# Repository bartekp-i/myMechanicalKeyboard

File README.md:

# 75% Custom Mechanical Keyboard PCB Documentation  
**A compact, RP2040-powered keyboard with USB-C and OLED support.**  

---

## Overview  
This project is a custom 75% mechanical keyboard PCB designed around the Raspberry Pi RP2040 microcontroller. It features a non-standard QWERTY layout with 83 keys, USB-C connectivity with robust signal filtering, ESD protection, and support for a 0.96-inch RGB OLED module. The PCB is manufactured by JLCPCB and ready for soldering and programming.  

---

## Features  
- **RP2040 Microcontroller**: Dual-core ARM Cortex-M0+ for flexible firmware customization.  
- **USB-C Connectivity**: Built-in signal filtering and ESD protection (TVS diode) on D+/D- lines.  
- **Power Regulation**: 3.3V LDO Regulator (SPX5205M5-L-3-3/TR) for stable power delivery.  
- **QSPI Flash**: W25Q16JVUXIQ (2MB) for firmware storage.  
- **Precision Timing**: ABM8-272-T3 12MHz crystal oscillator.  
- **OLED Support**: Pads/THT headers for a 0.96-inch RGB OLED module.  
- **Debugging**: SWD (Serial Wire Debug) pins for firmware flashing/troubleshooting.  
- **Mechanical Design**:  
  - 75% layout (83 keys).  
  - Custom plate and back panel.  
  - Stabilizers for Space, Shift, Enter, and Backspace keys.  
  - AKKO V3 Pro Yellow switches (pre-lubed linear).  
  - Switching diodes for every key (anti-ghosting).  

---

## Hardware Details  

### RP2040 Microcontroller  
- Handles key matrix scanning, USB communication, and peripheral control.  
- Connected peripherals:  
  - **QSPI Flash**: Stores firmware and configuration data.  
  - **ABM8-272-T3 Oscillator**: Provides precise timing for USB communication.  
  - **Boot Button**: For entering firmware update mode.  
  - **SWD Pins**: 1x3 header for programming/debugging.  

### USB-C and Signal Integrity  
- **ESD Protection**: TVS diodes on D+/D- lines to protect against electrostatic discharge.  
- **Filtering**: Ferrite beads/RC filters to reduce noise on data lines.  

### Power Regulation  
- **SPX5205M5-L-3-3/TR LDO**: Converts USB 5V to 3.3V for RP2040 and peripherals.  
- Max current: 150mA (sufficient for RP2040, OLED, and peripherals).  

### Keyboard Matrix  
- **83-Key Layout**: Non-standard 75% design (see `Layout/` directory for matrix mapping).  
- **Switching Diodes**: Each key has a diode (1N4148 or similar) to prevent "ghosting" by blocking reverse current in the matrix.  

### Stabilizers  
- Required for longer keys: Spacebar, Enter, Backspace, and Shift (supports Cherry-style stabilizers).  

### OLED Module  
- **0.96-inch RGB OLED**: Connected via SPI.  
- Mounting: THT pads or header pins for secure attachment.
- Finally I decided to not use it due to current draw considerations. 

---

## Design & Manufacturing  
- **PCB**: Designed in KiCad (files in `Hardware/`).   
- **Manufacturing**:  
  - JLCPCB 2-layer PCB with white solder mask finish.  
  - SMD components can be pre-soldered.  

---

## Firmware  
- Coded using *QMK*-RP2040 is compatible with this software.  
- Example firmware available in `Firmware/`.  

---

## Build Instructions  
1. **Solder Components**:  
   - Diodes (orient cathode stripe correctly).  
   - RP2040, USB-C port, oscillator, and regulator.  
   - SWD header and OLED pins.  
2. **Mount Stabilizers**: Clip-in Cherry stabilizers for large keys.  
3. **Install Switches**: Secure AKKO V3 Pro switches into the plate and solder to PCB.  
4. **Attach OLED**: Solder headers or directly mount the OLED module.  
5. **Flash Firmware**: Use SWD or UF2 bootloader (press boot button while plugging in USB).  

---

## Acknowledgements  
- JLCPCB for PCB manufacturing.  
- Raspberry Pi Foundation for RP2040.  

## 📸 Photos!  

**Keyboard layout** 

**Schematic** 

**PCB Layout**

**Keyboard Plate**

**Back Plate**

**3D PCB Layout**

**3D Keyboard Plate**

**3D Back Plate**

**Boards After Manufacturing**

**Fully Assembled Product**

---  
*Designed with Kicad by Bartosz Piotrowski.*

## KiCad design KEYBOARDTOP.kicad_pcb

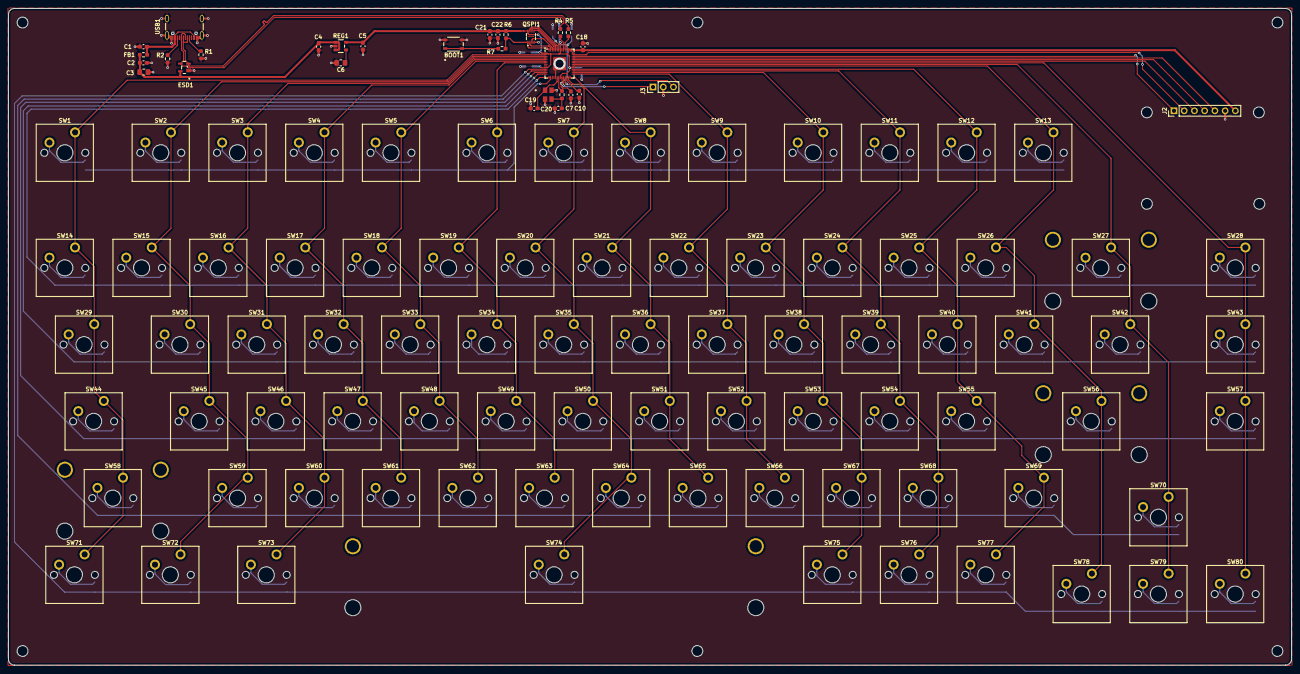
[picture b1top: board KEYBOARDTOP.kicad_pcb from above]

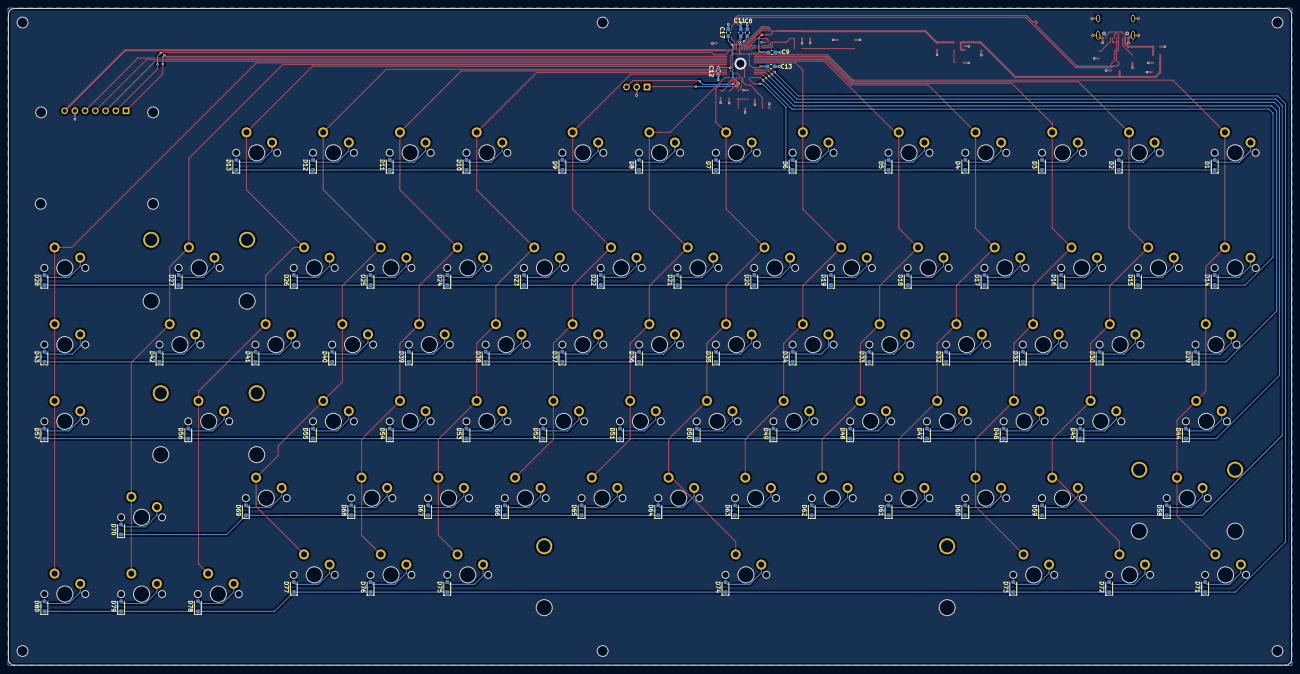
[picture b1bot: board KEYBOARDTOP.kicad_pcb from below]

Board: 2 copper layers, 318.5 x 163.0 mm, 200 parts (86 on the bottom side), 130 nets.

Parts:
BOOT1: SKRPABE010; SW4_SKRPABE010_ALPS
C1: 10nF; C_0603_1608Metric_Pad1.08x0.95mm_HandSolder
C2: 0.1uF; C_0603_1608Metric_Pad1.08x0.95mm_HandSolder
C3: 10uF; C_0805_2012Metric_Pad1.18x1.45mm_HandSolder
C4, C5: 1uF; C_0603_1608Metric_Pad1.08x0.95mm_HandSolder
C6: NO-FIT(10u); C_0805_2012Metric_Pad1.18x1.45mm_HandSolder
C7, C8, C9, C10, C11, C12, C13, C21: 100n; C_0603_1608Metric_Pad1.08x0.95mm_HandSolder
C17, C18: 1u; C_0603_1608Metric_Pad1.08x0.95mm_HandSolder
C19, C20: 15pF; C_0603_1608Metric_Pad1.08x0.95mm_HandSolder
C22: 2u2; C_0603_1608Metric_Pad1.08x0.95mm_HandSolder
D1, D2, D3, D4, D5, D6, D7, D8, D9, D10, D11, D12, D13, D14, D15, D16, D17, D18, D19, D20, D21, D22, D23, D24, D25, D26, D27, D28, D29, D30, D31, D32, D33, D34, D35, D36, D37, D38, D39, D40, D41, D42, D43, D44, D45, D46, D47, D48, D49, D50, D51, D52, D53, D54, D55, D56, D57, D58, D59, D60, D61, D62, D63, D64, D65, D66, D67, D68, D69, D70, D71, D72, D73, D74, D75, D76, D77, D78, D79, D80: D_Small; D_SOD-323_HandSoldering
ESD1: PRTR5V0U2X_215; SOT143B_PRTR5V0U2X_215_NEX
FB1: 120/100MHZ; R_0603_1608Metric_Pad0.98x0.95mm_HandSolder
J2: Conn_01x07; PinHeader_1x07_P2.54mm_Vertical
J3: Conn_01x03; PinHeader_1x03_P2.54mm_Vertical
QSPI1: W25Q16JVUXIQ; W25Q16JVUXIQ_WIN
R1, R2: 5.1k; R_0603_1608Metric_Pad0.98x0.95mm_HandSolder
R3: 1k; R_0603_1608Metric_Pad0.98x0.95mm_HandSolder
R4, R5: 27R; R_0603_1608Metric_Pad0.98x0.95mm_HandSolder
R6: No-Fit(1k); R_0603_1608Metric_Pad0.98x0.95mm_HandSolder
R7: 1K; R_0603_1608Metric_Pad0.98x0.95mm_HandSolder
REG1: SPX5205M5-L-3-3/TR; SP6201EM5
S1: MX_stab; STAB_MX_P_6.25u
S2: MX_stab; STAB_MX_P_2u
S3, S4: MX_stab; STAB_MX_P_2.25u
SW1: ESC; SW_Cherry_MX_PCB_1.00u
SW2: F1; SW_Cherry_MX_PCB_1.00u
SW3: F2; SW_Cherry_MX_PCB_1.00u
SW4: F3; SW_Cherry_MX_PCB_1.00u
SW5: F4; SW_Cherry_MX_PCB_1.00u
SW6: F5; SW_Cherry_MX_PCB_1.00u
SW7: F6; SW_Cherry_MX_PCB_1.00u
SW8: F7; SW_Cherry_MX_PCB_1.00u
SW9: F8; SW_Cherry_MX_PCB_1.00u
SW10: F9; SW_Cherry_MX_PCB_1.00u
SW11: F10; SW_Cherry_MX_PCB_1.00u
SW12: F11; SW_Cherry_MX_PCB_1.00u
SW13: F12; SW_Cherry_MX_PCB_1.00u
SW14: "~`"; SW_Cherry_MX_PCB_1.00u
SW15: 1; SW_Cherry_MX_PCB_1.00u
SW16: 2; SW_Cherry_MX_PCB_1.00u
SW17: 3; SW_Cherry_MX_PCB_1.00u
SW18: 4; SW_Cherry_MX_PCB_1.00u
SW19: 5; SW_Cherry_MX_PCB_1.00u
SW20: 6; SW_Cherry_MX_PCB_1.00u
SW21: 7; SW_Cherry_MX_PCB_1.00u
SW22: 8; SW_Cherry_MX_PCB_1.00u
SW23: 9; SW_Cherry_MX_PCB_1.00u
SW24: 0; SW_Cherry_MX_PCB_1.00u
SW25: -; SW_Cherry_MX_PCB_1.00u
SW26: +; SW_Cherry_MX_PCB_1.00u
SW27: backspace; SW_Cherry_MX_PCB_2.00u
SW28: pg_up; SW_Cherry_MX_PCB_1.00u
SW29: tab; SW_Cherry_MX_PCB_1.50u
SW30: q; SW_Cherry_MX_PCB_1.00u
SW31: w; SW_Cherry_MX_PCB_1.00u
SW32: e; SW_Cherry_MX_PCB_1.00u
SW33: r; SW_Cherry_MX_PCB_1.00u
SW34: t; SW_Cherry_MX_PCB_1.00u
SW35: y; SW_Cherry_MX_PCB_1.00u
SW36: u; SW_Cherry_MX_PCB_1.00u
SW37: i; SW_Cherry_MX_PCB_1.00u
SW38: o; SW_Cherry_MX_PCB_1.00u
SW39: p; SW_Cherry_MX_PCB_1.00u
SW40: [; SW_Cherry_MX_PCB_1.00u
SW41: ]; SW_Cherry_MX_PCB_1.00u
SW42: |; SW_Cherry_MX_PCB_1.50u
SW43: pg_down; SW_Cherry_MX_PCB_1.00u
SW44: caps; SW_Cherry_MX_PCB_1.75u
SW45: a; SW_Cherry_MX_PCB_1.00u
SW46: s; SW_Cherry_MX_PCB_1.00u
SW47: d; SW_Cherry_MX_PCB_1.00u
SW48: f; SW_Cherry_MX_PCB_1.00u
SW49: g; SW_Cherry_MX_PCB_1.00u
SW50: h; SW_Cherry_MX_PCB_1.00u
SW51: j; SW_Cherry_MX_PCB_1.00u
SW52: k; SW_Cherry_MX_PCB_1.00u
SW53: l; SW_Cherry_MX_PCB_1.00u
SW54: :; SW_Cherry_MX_PCB_1.00u
SW55: "; SW_Cherry_MX_PCB_1.00u
SW56: enter; SW_Cherry_MX_PCB_2.25u
SW57: delete; SW_Cherry_MX_PCB_1.00u
SW58: shift; SW_Cherry_MX_PCB_2.25u
SW59: z; SW_Cherry_MX_PCB_1.00u
SW60: x; SW_Cherry_MX_PCB_1.00u
SW61: c; SW_Cherry_MX_PCB_1.00u
SW62: v; SW_Cherry_MX_PCB_1.00u
SW63: b; SW_Cherry_MX_PCB_1.00u
SW64: n; SW_Cherry_MX_PCB_1.00u
SW65: m; SW_Cherry_MX_PCB_1.00u
SW66: <; SW_Cherry_MX_PCB_1.00u
SW67: >; SW_Cherry_MX_PCB_1.00u
SW68: ?; SW_Cherry_MX_PCB_1.00u
SW69: shift_2; SW_Cherry_MX_PCB_1.75u
SW70: arrow_up; SW_Cherry_MX_PCB_1.00u
SW71: ctrl; SW_Cherry_MX_PCB_1.25u
SW72: windows; SW_Cherry_MX_PCB_1.25u
SW73: alt; SW_Cherry_MX_PCB_1.25u
SW74: spacebar; SW_Cherry_MX_PCB_6.25u
SW75: alt; SW_Cherry_MX_PCB_1.00u
SW76: fn; SW_Cherry_MX_PCB_1.00u
SW77: ctrl; SW_Cherry_MX_PCB_1.00u
SW78: arrow_left; SW_Cherry_MX_PCB_1.00u
SW79: arrow_down; SW_Cherry_MX_PCB_1.00u
SW80: arrow_right; SW_Cherry_MX_PCB_1.00u
U3: RP2040; QFN-56-1EP_7x7mm_P0.4mm_EP3.2x3.2mm
USB1: USB_C_Receptacle_USB2.0_16P; USB_C_Receptacle_GCT_USB4105-xx-A_16P_TopMnt_Horizontal
X1: ABM8-272-T3; ABM8-272-T3_ABR

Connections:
+1.1V: C7.1, C8.1, C17.1, U3.23 (DVDD), U3.45 (VREG_VOUT), U3.50 (DVDD)
+3.3V: C5.1, C9.1, C10.1, C11.1, C12.1, C13.1, C18.1, C21.1, C22.1, J2.7, QSPI1.8 (VCC), R6.2, REG1.5 (OUT), U3.1 (IOVDD), U3.10 (IOVDD), U3.22 (IOVDD), U3.26 (RUN), U3.33 (IOVDD), U3.42 (IOVDD), U3.43 (ADC_AVDD), U3.44 (VREG_IN), U3.48 (USB_VDD), U3.49 (IOVDD)
+5V: C2.1, C3.1, C4.1, ESD1.4, FB1.2, REG1.1 (IN), REG1.3 (EN)
/D+: ESD1.3, R4.1, USB1.A6 (D+), USB1.B6 (D+)
/D-: ESD1.2, R5.1, USB1.A7 (D-), USB1.B7 (D-)
/QSPI_SCLK: QSPI1.6 (CLK), U3.52 (QSPI_SCLK)
/QSPI_SD0: QSPI1.5 (DI(IO0)), U3.53 (QSPI_SD0)
/QSPI_SD1: QSPI1.2 (DO(IO1)), U3.55 (QSPI_SD1)
/QSPI_SD2: QSPI1.3 (/WP(IO2)), U3.54 (QSPI_SD2)
/QSPI_SD3: QSPI1.7 (/HOLD_or_/RESET(IO3)), U3.51 (QSPI_SD3)
/QSPI_SS: QSPI1.1 (/CS), R6.1, R7.1, U3.56 (QSPI_SS)
/SWCLK: J3.1, U3.24 (SWCLK)
/SWDIO: J3.3, U3.25 (SWD)
/USB+: R4.2, U3.47 (USB+)
/USB-: R5.2, U3.46 (USB-)
CS: J2.3, U3.37 (GPIO25)
DIN: J2.5, U3.39 (GPIO27_ADC1)
DS: J2.2, U3.41 (GPIO29_ADC3)
GND: BOOT1.3, BOOT1.4, C1.2, C2.2, C3.2, C4.2, C5.2, C6.2, C7.2, C8.2, C9.2, C10.2, C11.2, C12.2, C13.2, C17.2, C18.2, C19.2, C20.2, C21.2, C22.2, ESD1.1, J2.6, J3.2, QSPI1.4 (GND), R1.1, R2.2, REG1.2 (GND), U3.19 (TESTEN), U3.57 (GND), USB1.A1 (GND), USB1.A12 (GND), USB1.B1 (GND), USB1.B12 (GND), USB1.S1 (SHIELD), X1.2, X1.4
unnamed: BOOT1.1, BOOT1.2, R7.2
unnamed: C20.1, R3.2, X1.3
unnamed: D1.2 (A), SW1.1
unnamed: D2.2 (A), SW2.1
unnamed: D3.2 (A), SW3.1
unnamed: D4.2 (A), SW4.1
unnamed: D5.2 (A), SW5.1
unnamed: D6.2 (A), SW6.1
unnamed: D7.2 (A), SW7.1
unnamed: D8.2 (A), SW8.1
unnamed: D9.2 (A), SW9.1
unnamed: D10.2 (A), SW10.1
unnamed: D11.2 (A), SW11.1
unnamed: D12.2 (A), SW12.1
unnamed: D13.2 (A), SW13.1
unnamed: D14.2 (A), SW14.1
unnamed: D15.2 (A), SW15.1
unnamed: D16.2 (A), SW16.1
unnamed: D17.2 (A), SW17.1
unnamed: D18.2 (A), SW18.1
unnamed: D19.2 (A), SW19.1
unnamed: D20.2 (A), SW20.1
unnamed: D21.2 (A), SW21.1
unnamed: D22.2 (A), SW22.1
unnamed: D23.2 (A), SW23.1
unnamed: D24.2 (A), SW24.1
unnamed: D25.2 (A), SW25.1
unnamed: D26.2 (A), SW26.1
unnamed: D27.2 (A), SW27.1
unnamed: D28.2 (A), SW28.1
unnamed: D29.2 (A), SW29.1
unnamed: D30.2 (A), SW30.1
unnamed: D31.2 (A), SW31.1
unnamed: D32.2 (A), SW32.1
unnamed: D33.2 (A), SW33.1
unnamed: D34.2 (A), SW34.1
unnamed: D35.2 (A), SW35.1
unnamed: D36.2 (A), SW36.1
unnamed: D37.2 (A), SW37.1
unnamed: D38.2 (A), SW38.1
unnamed: D39.2 (A), SW39.1
unnamed: D40.2 (A), SW40.1
unnamed: D41.2 (A), SW41.1
unnamed: D42.2 (A), SW42.1
unnamed: D43.2 (A), SW43.1
unnamed: D44.2 (A), SW44.1
unnamed: D45.2 (A), SW45.1
unnamed: D46.2 (A), SW46.1
unnamed: D47.2 (A), SW47.1
unnamed: D48.2 (A), SW48.1
unnamed: D49.2 (A), SW49.1
unnamed: D50.2 (A), SW50.1
unnamed: D51.2 (A), SW51.1
unnamed: D52.2 (A), SW52.1
unnamed: D53.2 (A), SW53.1
unnamed: D54.2 (A), SW54.1
unnamed: D55.2 (A), SW55.1
unnamed: D56.2 (A), SW56.1
unnamed: D57.2 (A), SW57.1
unnamed: D58.2 (A), SW58.1
unnamed: D59.2 (A), SW59.1
unnamed: D60.2 (A), SW60.1
unnamed: D61.2 (A), SW61.1
unnamed: D62.2 (A), SW62.1
unnamed: D63.2 (A), SW63.1
unnamed: D64.2 (A), SW64.1
unnamed: D65.2 (A), SW65.1
unnamed: D66.2 (A), SW66.1
unnamed: D67.2 (A), SW67.1
unnamed: D68.2 (A), SW68.1
unnamed: D69.2 (A), SW69.1
unnamed: D70.2 (A), SW70.1
unnamed: D71.2 (A), SW71.1
unnamed: D72.2 (A), SW72.1
unnamed: D73.2 (A), SW73.1
unnamed: D74.2 (A), SW74.1
unnamed: D75.2 (A), SW75.1
unnamed: D76.2 (A), SW76.1
unnamed: D77.2 (A), SW77.1
unnamed: D78.2 (A), SW78.1
unnamed: D79.2 (A), SW79.1
unnamed: D80.2 (A), SW80.1
unnamed: C6.1, REG1.4 (RST/ADJ)
unnamed: R1.2, USB1.A5 (CC1)
unnamed: R2.1, USB1.B5 (CC2)
RST: J2.1, U3.40 (GPIO28_ADC2)
SCK: J2.4, U3.38 (GPIO26_ADC0)
Vbus: C1.1, FB1.1, USB1.A4 (VBUS), USB1.A9 (VBUS), USB1.B4 (VBUS), USB1.B9 (VBUS)
XIN: C19.1, U3.20 (XIN), X1.1
XOUT: R3.1, U3.21 (XOUT)
col0: SW1.2, SW14.2, SW29.2, SW44.2, SW58.2, SW71.2, U3.2 (GPIO0)
col1: SW2.2, SW15.2, SW30.2, SW45.2, SW59.2, SW72.2, U3.3 (GPIO1)
col2: SW3.2, SW16.2, SW31.2, SW46.2, SW60.2, SW73.2, U3.4 (GPIO2)
col3: SW4.2, SW17.2, SW32.2, SW47.2, SW61.2, U3.5 (GPIO3)
col4: SW5.2, SW18.2, SW33.2, SW48.2, SW62.2, U3.6 (GPIO4)
col5: SW6.2, SW19.2, SW34.2, SW49.2, SW63.2, U3.7 (GPIO5)
col6: SW7.2, SW20.2, SW35.2, SW50.2, SW64.2, SW74.2, U3.27 (GPIO16)
col7: SW8.2, SW21.2, SW36.2, SW51.2, SW65.2, U3.28 (GPIO17)
col8: SW9.2, SW22.2, SW37.2, SW52.2, SW66.2, U3.29 (GPIO18)
col9: SW10.2, SW23.2, SW38.2, SW53.2, SW67.2, SW75.2, U3.30 (GPIO19)
col10: SW11.2, SW24.2, SW39.2, SW54.2, SW68.2, SW76.2, U3.31 (GPIO20)
col11: SW12.2, SW25.2, SW40.2, SW55.2, SW69.2, SW77.2, U3.32 (GPIO21)
col12: SW13.2, SW26.2, SW41.2, SW56.2, SW78.2, U3.34 (GPIO22)
col13: SW27.2, SW42.2, SW70.2, SW79.2, U3.35 (GPIO23)
col14: SW28.2, SW43.2, SW57.2, SW80.2, U3.36 (GPIO24)
row0: D1.1 (K), D2.1 (K), D3.1 (K), D4.1 (K), D5.1 (K), D6.1 (K), D7.1 (K), D8.1 (K), D9.1 (K), D10.1 (K), D11.1 (K), D12.1 (K), D13.1 (K), U3.16 (GPIO13)
row1: D14.1 (K), D15.1 (K), D16.1 (K), D17.1 (K), D18.1 (K), D19.1 (K), D20.1 (K), D21.1 (K), D22.1 (K), D23.1 (K), D24.1 (K), D25.1 (K), D26.1 (K), D27.1 (K), D28.1 (K), U3.15 (GPIO12)
row2: D29.1 (K), D30.1 (K), D31.1 (K), D32.1 (K), D33.1 (K), D34.1 (K), D35.1 (K), D36.1 (K), D37.1 (K), D38.1 (K), D39.1 (K), D40.1 (K), D41.1 (K), D42.1 (K), D43.1 (K), U3.14 (GPIO11)
row3: D44.1 (K), D45.1 (K), D46.1 (K), D47.1 (K), D48.1 (K), D49.1 (K), D50.1 (K), D51.1 (K), D52.1 (K), D53.1 (K), D54.1 (K), D55.1 (K), D56.1 (K), D57.1 (K), U3.13 (GPIO10)
row4: D58.1 (K), D59.1 (K), D60.1 (K), D61.1 (K), D62.1 (K), D63.1 (K), D64.1 (K), D65.1 (K), D66.1 (K), D67.1 (K), D68.1 (K), D69.1 (K), D70.1 (K), U3.12 (GPIO9)
row5: D71.1 (K), D72.1 (K), D73.1 (K), D74.1 (K), D75.1 (K), D76.1 (K), D77.1 (K), D78.1 (K), D79.1 (K), D80.1 (K), U3.11 (GPIO8)

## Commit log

2025-05-25 LICENSE
2025-05-25 Create Read
